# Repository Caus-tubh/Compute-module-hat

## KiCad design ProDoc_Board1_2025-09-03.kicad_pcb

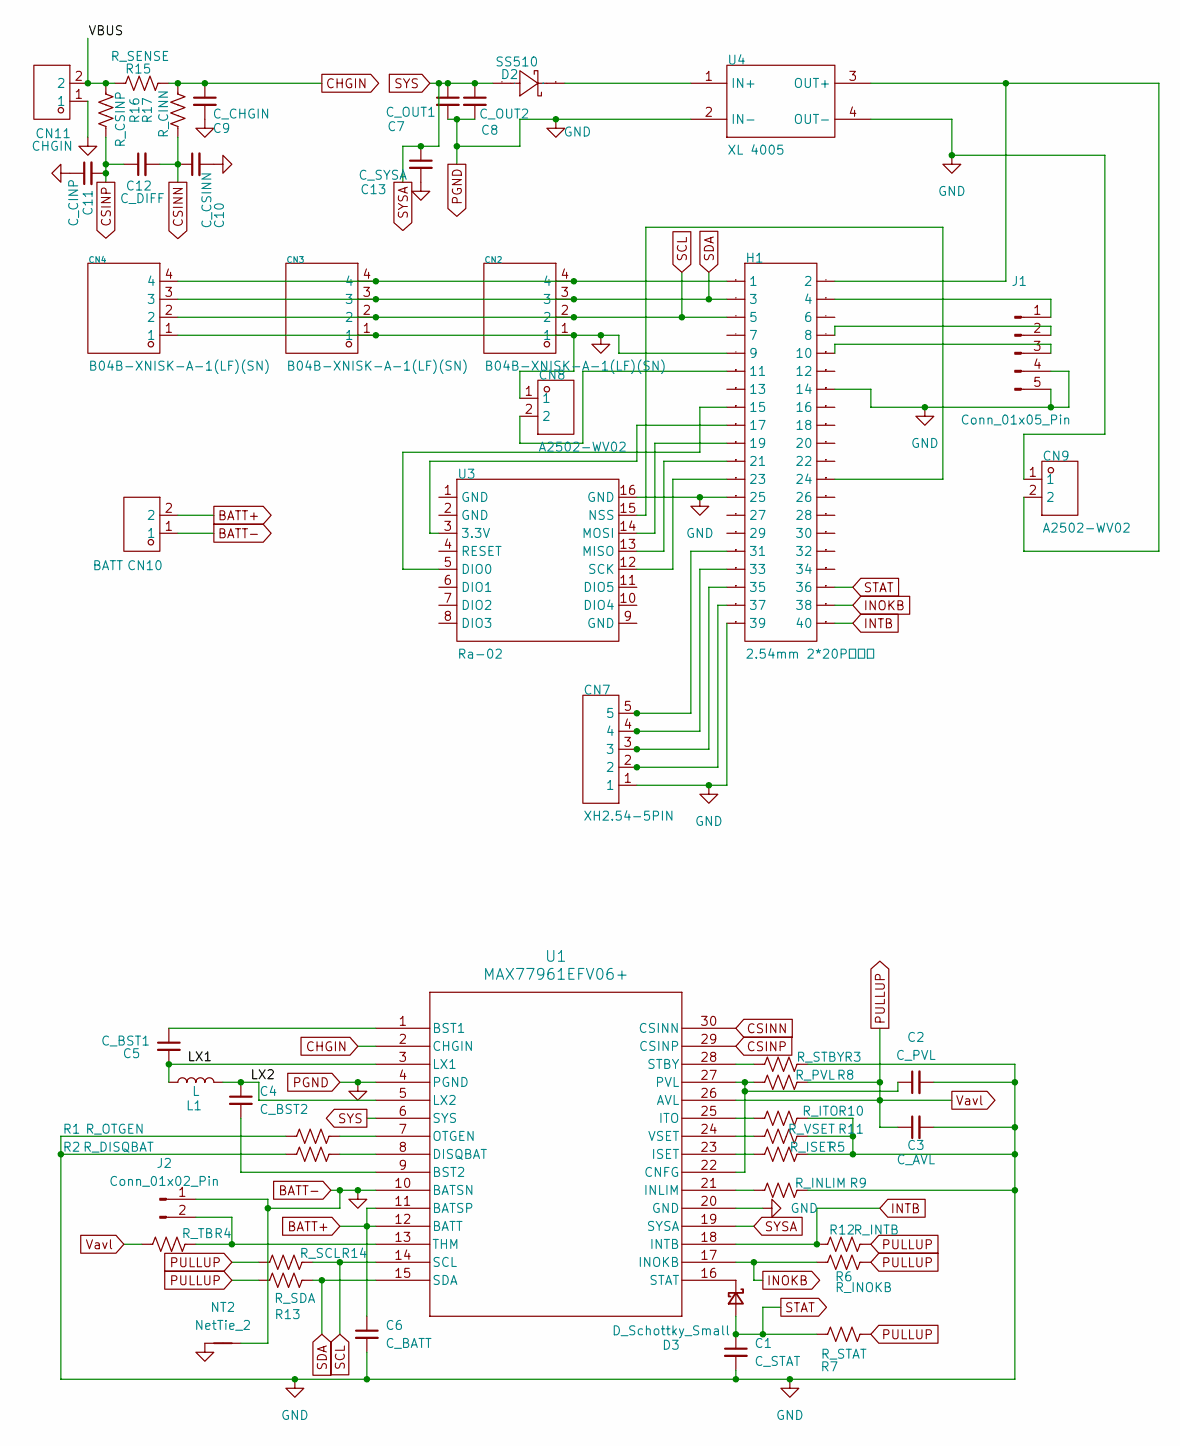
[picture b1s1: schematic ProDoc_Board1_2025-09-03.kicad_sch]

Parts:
C1: C_STAT; C_1210_3225Metric
C2: C_PVL; C_0402_1005Metric
C3: C_AVL; C_0402_1005Metric
C4: C_BST2; C_0402_1005Metric
C5: C_BST1; C_0402_1005Metric
C6: C_BATT; C_0805_2012Metric
C7: C_OUT1; C_1210_3225Metric
C8: C_OUT2; C_1210_3225Metric
C9: C_CHGIN; C_1210_3225Metric
C10: C_CSINN; C_0402_1005Metric
C11: C_CINP; C_0402_1005Metric
C12: C_DIFF; C_0402_1005Metric
C13: C_SYSA; C_0402_1005Metric
CN2, CN3, CN4: B04B-XNISK-A-1(LF)(SN); JST_SH_BM04B-SRSS-TB_1x04-1MP_P1.00mm_Vertical; Manufacturer Part B04B-XNISK-A-1(LF)(SN); LCSC Part Name 1x4P 间距:2.5mm
CN7: XH2.54-5PIN; JST_SH_BM05B-SRSS-TB_1x05-1MP_P1.00mm_Vertical; Manufacturer Part XH2.54-5PIN; LCSC Part Name XH2.54-5PIN
CN8, CN9: A2502-WV02; JST_SH_BM02B-SRSS-TB_1x02-1MP_P1.00mm_Vertical; Manufacturer Part A2502-WV02; LCSC Part Name A2502-WV02
CN10: BATT; JST_XH_B2B-XH-A_1x02_P2.50mm_Vertical; Manufacturer Part A2502-WV02; LCSC Part Name A2502-WV02
CN11: CHGIN; JST_XH_B2B-XH-A_1x02_P2.50mm_Vertical; Manufacturer Part A2502-WV02; LCSC Part Name A2502-WV02
D2: SS510; SMA_L4.3-W2.6-LS5.0-RD; Manufacturer Part SS510; LCSC Part Name 电压:100V 电流:5A
D3: D_Schottky_Small; D_SOD-323
H1: 2.54mm 2*20P直排针; HDR-TH_40P-P2.54-V-M-R2-C20-S2.54; Manufacturer Part 2.54mm 2*20P直排针; LCSC Part Name 2x20P 间距:2.54mm 方针 直插
J1: Conn_01x05_Pin; JST_SH_BM05B-SRSS-TB_1x05-1MP_P1.00mm_Vertical
J2: Conn_01x02_Pin; JST_SH_BM02B-SRSS-TB_1x02-1MP_P1.00mm_Vertical
L1: L; CMLE063T-2R2MS
NT2: NetTie_2
R1: R_OTGEN; R_0402_1005Metric
R2: R_DISQBAT; R_0402_1005Metric
R3: R_STBY; R_0402_1005Metric
R4: R_TB; R_0402_1005Metric
R5: R_ISET; R_0402_1005Metric
R6: R_INOKB; R_0402_1005Metric
R7: R_STAT; R_0402_1005Metric
R8: R_PVL; R_0402_1005Metric
R9: R_INLIM; R_0402_1005Metric
R10: R_ITO; R_0402_1005Metric
R11: R_VSET; R_0402_1005Metric
R12: R_INTB; R_0402_1005Metric
R13: R_SDA; R_0402_1005Metric
R14: R_SCL; R_0402_1005Metric
R15: R_SENSE; R_1206_3216Metric
R16: R_CSINP; R_0402_1005Metric
R17: R_CINN; R_0402_1005Metric
U1: MAX77961EFV06+; MAX77961
U3: Ra-02; WIRELM-SMD_RA-02-BL; Manufacturer Part Ra-02; LCSC Part Name 433MHz LORA扩频无线模块 超远10KM SX1278
U4: XL 4005; COMM-SMD_MINI5605V5A; Manufacturer Part mini5605V5A输出电源模块; LCSC Part Name mini5605V5A输出电源模块

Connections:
/LX1: C5.2, L1.1, U1.3 (LX1)
/LX2: C4.1, L1.2, U1.5 (LX2)
/VBUS: CN11.2, R15.1, R16.2
BATT+: C6.1, CN10.2, U1.11 (BATSP), U1.12 (BATT)
BATT-: C1.2, C2.2, C3.2, C6.2, C7.2, C8.2, C9.2, C10.2, C11.1, C13.2, CN2.1, CN3.1, CN4.1, CN7.1, CN8.1, CN9.1, CN10.1, CN11.1, H1.9, H1.14, H1.25, H1.39, J1.4, J1.5, J2.1, NT2.1, NT2.2, R1.1, R2.1, R3.2, R5.2, R9.2, R10.2, R11.2, U1.4 (PGND), U1.10 (BATSN), U1.20 (GND), U3.16 (GND), U4.2 (IN-), U4.4 (OUT-)
CHGIN: C9.1, R15.2, R17.2, U1.2 (CHGIN)
CSINN: C10.1, C12.2, R17.1, U1.30 (CSINN)
CSINP: C11.2, C12.1, R16.1, U1.29 (CSINP)
INOKB: H1.38, R6.1, U1.17 (INOKB)
INTB: H1.40, R12.1, U1.18 (INTB)
unnamed: CN2.4, CN3.4, CN4.4, H1.1
unnamed: CN7.2, H1.37
unnamed: CN7.3, H1.35
unnamed: CN7.4, H1.33
unnamed: CN7.5, H1.31
unnamed: CN8.2, H1.11
unnamed: D2.1 (K), U4.1 (IN+)
unnamed: D3.1 (K), U1.16 (STAT)
unnamed: H1.4, J1.1
unnamed: H1.8, J1.2
unnamed: H1.10, J1.3
unnamed: J2.2, R4.2, U1.13 (THM)
unnamed: C5.1, U1.1 (BST1)
unnamed: C4.2, U1.9 (BST2)
unnamed: C2.1, R8.1, U1.22 (CNFG), U1.27 (PVL)
unnamed: R2.2, U1.8 (DISQBAT)
unnamed: R9.1, U1.21 (INLIM)
unnamed: R5.1, U1.23 (ISET)
unnamed: R10.1, U1.25 (ITO)
unnamed: R1.2, U1.7 (OTGEN)
unnamed: R3.1, U1.28 (STBY)
unnamed: R11.1, U1.24 (VSET)
unnamed: H1.17, U3.3 (3.3V)
unnamed: H1.15, U3.5 (DIO0)
unnamed: H1.21, U3.13 (MISO)
unnamed: H1.19, U3.14 (MOSI)
unnamed: H1.24, U3.15 (NSS)
unnamed: H1.23, U3.12 (SCK)
unnamed: CN9.2, H1.2, U4.3 (OUT+)
PULLUP: C3.1, R4.1, R6.2, R7.2, R8.2, R12.2, R13.1, R14.1, U1.26 (AVL)
SCL: CN2.2, CN3.2, CN4.2, H1.5, R14.2, U1.14 (SCL)
SDA: CN2.3, CN3.3, CN4.3, H1.3, R13.2, U1.15 (SDA)
STAT: C1.1, D3.2 (A), H1.36, R7.1
SYS: C7.1, C8.1, C13.1, D2.2 (A), U1.6 (SYS), U1.19 (SYSA)

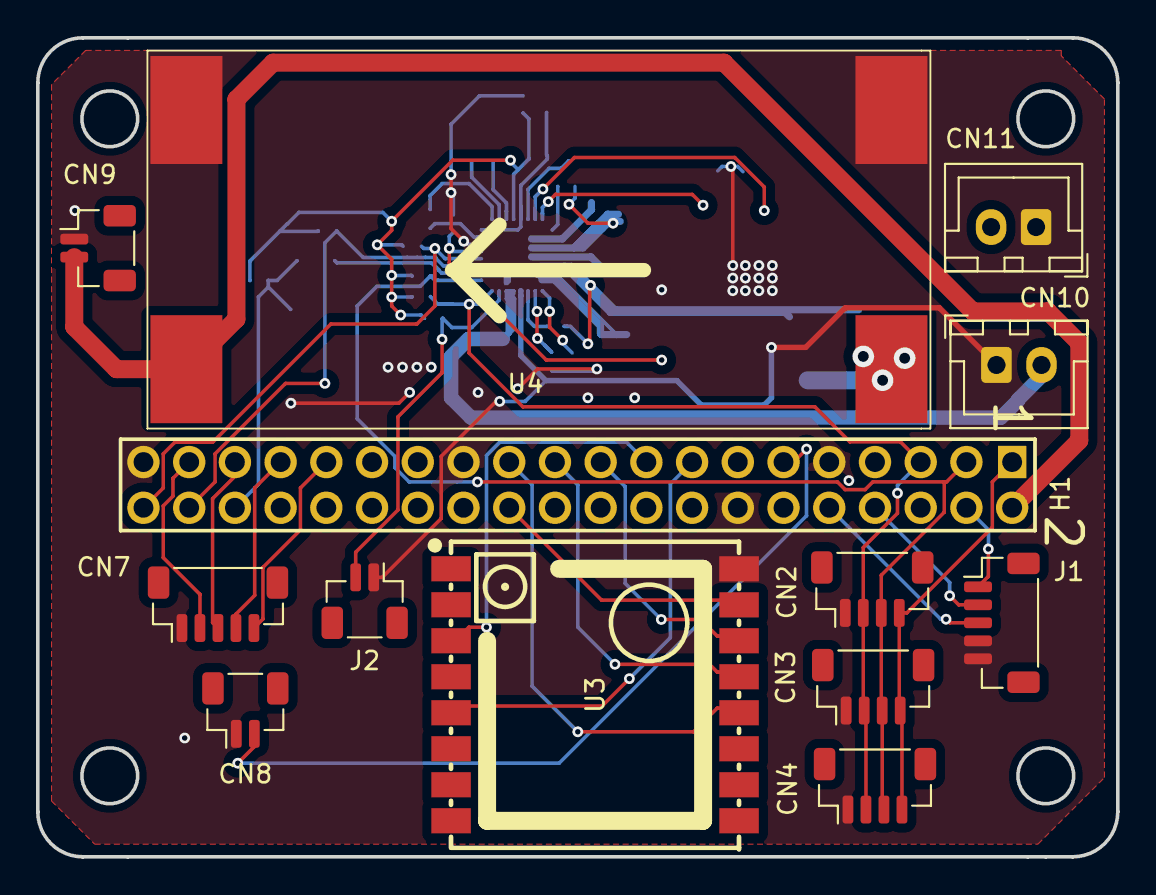
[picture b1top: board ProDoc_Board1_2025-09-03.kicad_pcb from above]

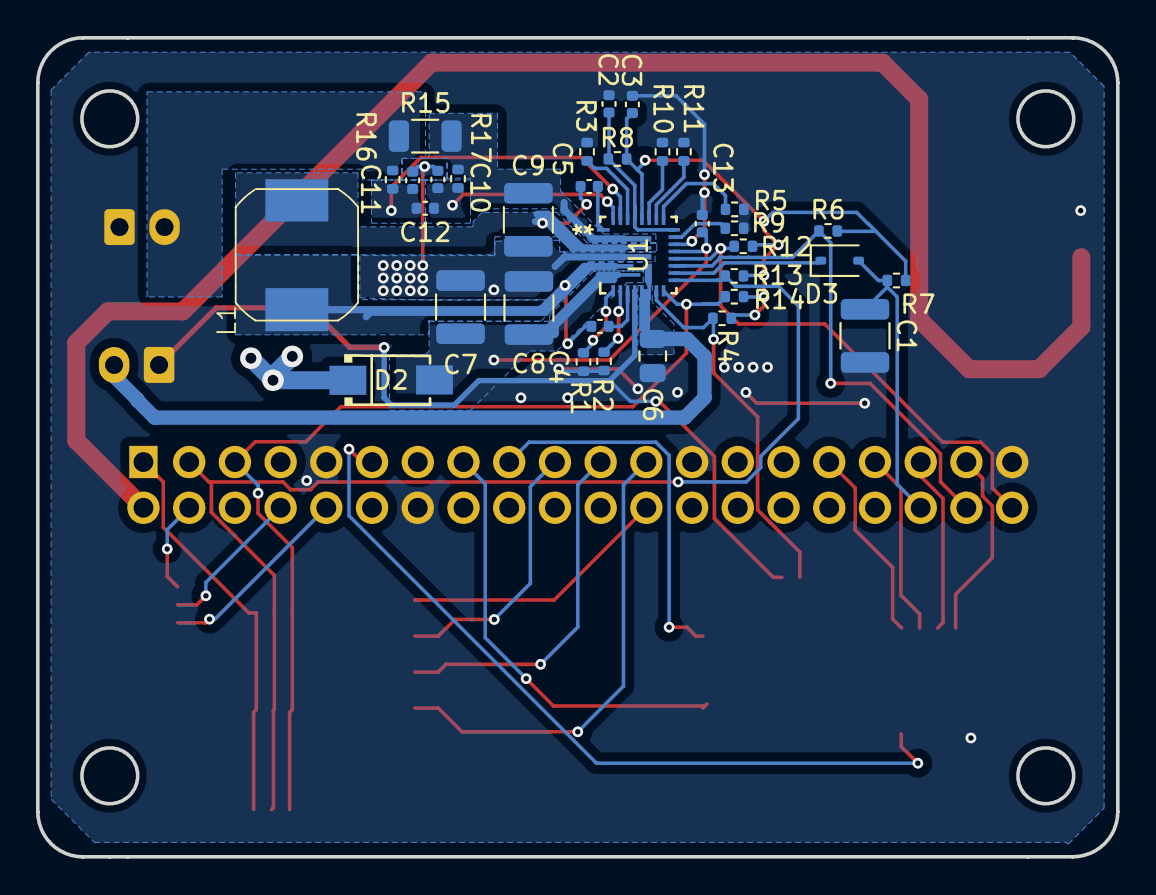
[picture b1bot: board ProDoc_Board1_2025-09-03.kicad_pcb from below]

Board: 2 copper layers, 60.0 x 45.5 mm, 47 parts (34 on the bottom side), 44 nets.

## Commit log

2025-09-17 init
2025-09-17 added IC
2025-09-24 schenatic done
2025-09-24 layout started
2025-09-25 temp
2025-10-06 v1.2.0
2026-03-04 fixed grounds
